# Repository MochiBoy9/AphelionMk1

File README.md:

# AphelionMk1
whoa! cool hack club project i'm making as a starter to cad and stuff

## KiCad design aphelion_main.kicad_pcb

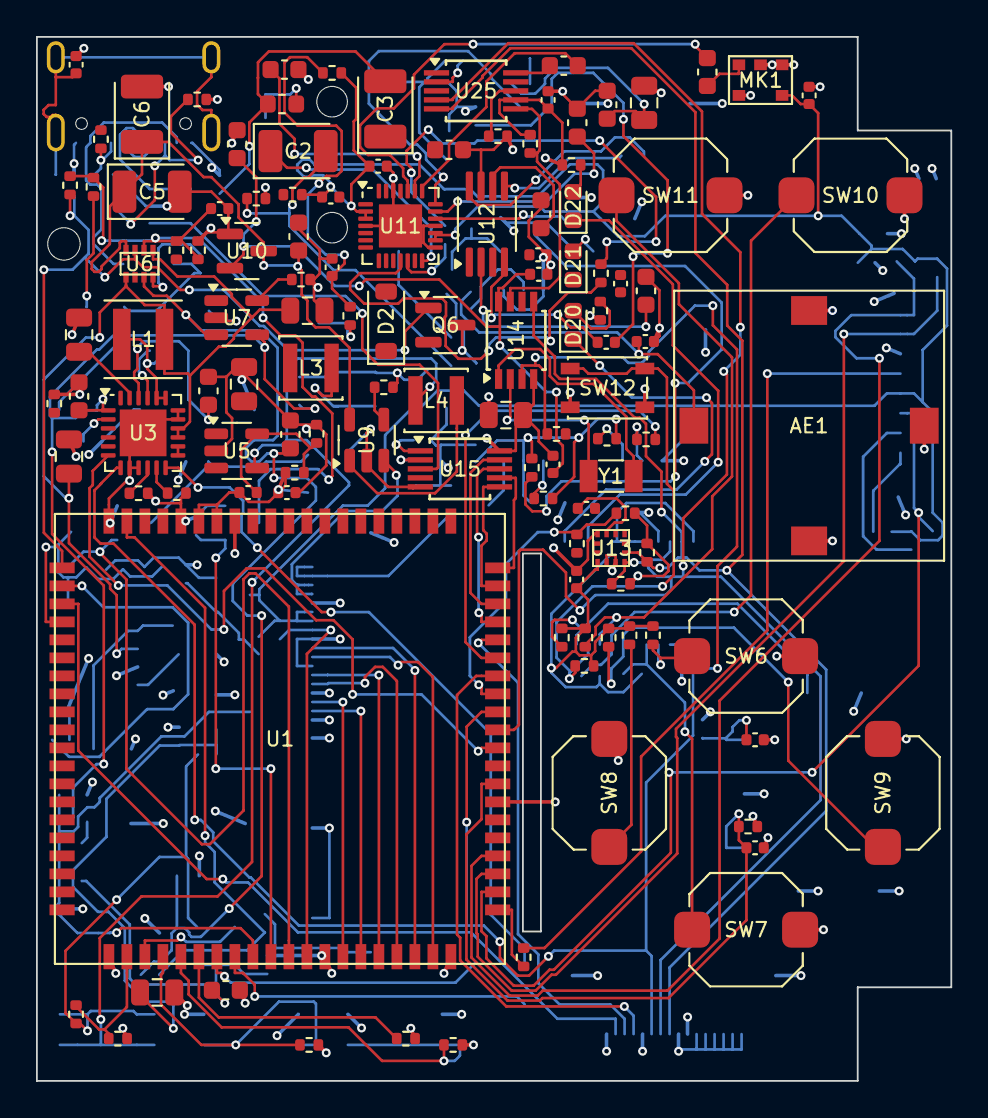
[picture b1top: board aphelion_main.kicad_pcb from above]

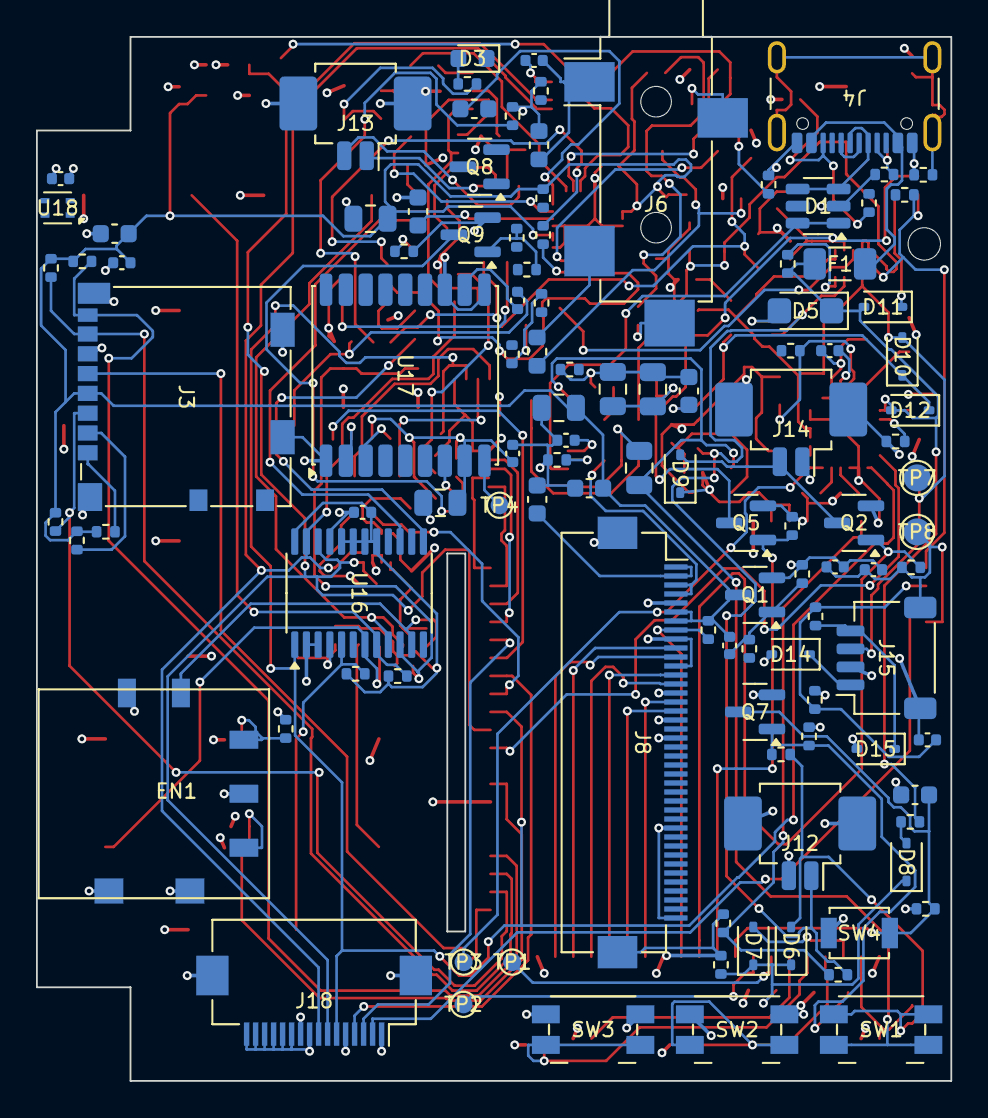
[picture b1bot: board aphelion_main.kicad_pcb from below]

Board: 4 copper layers, 50.8 x 58.0 mm, 232 parts (111 on the bottom side), 157 nets.

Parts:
AE1: 15 x 15 x 4 mm ceramic patch, 1575 MHz, surface m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; PATCH_15_SMD
C2, C3, C5, C6: 220 uF; CP_EIA-3528-15_AVX-H
C101: 4.7n; C_0402_1005Metric
C102, C111, C122, C124, C125, C126, C129, C130, C131, C132, C136, C137, C141, C145, C152, C153, C157, C158, C159, C160, C164: 100n; C_0402_1005Metric
C103, C112, C113, C118, C120, C121, C128, C142, C143, C146, C155, C156, C161, C162: 1u; C_0603_1608Metric
C104, C107, C108, C109, C114, C119, C123, C127, C135, C154, C163: 10u; C_0805_2012Metric
C105, C148, C165: 4.7u; C_0603_1608Metric
C106: 47n; C_0402_1005Metric
C110, C133, C134: 10n; C_0402_1005Metric
C115, C116: 22u; C_0805_2012Metric
C117: 22p; C_0402_1005Metric
C138, C144: 100p; C_0402_1005Metric
C139, C140: not fitted (tuning); C_0402_1005Metric
C147: 1u 50V; C_0603_1608Metric
C149, C150, C151: 10u; C_0603_1608Metric
D1: USBLC6-2SC6; SOT-23-6
D2: B0540W; D_SOD-123
D3: amber; LED_0603_1608Metric
D5: SMF12A; D_SMF
D6, D7, D8, D9, D11: 1N4148W; D_SOD-323
D10, D12: BAT54; D_SOD-323
D14, D15: ESD; D_SOD-323
D20: green; LED_0603_1608Metric
D21: red; LED_0603_1608Metric
D22: blue; LED_0603_1608Metric
EN1: thumbwheel encoder with push; THUMBWHEEL_ENC
F1: 2 A PTC; Fuse_1206_3216Metric
FB1: ferrite bead, 0402; R_0402_1005Metric
H1: M1.6 clamp screw; HOLE_1.8
J3: 104031-0811; microSD_HC_Molex_104031-0811
J4: USB4105-GF-A; USB_C_Receptacle_GCT_USB4105-xx-A_16P_TopMnt_Horizontal
J6: SJ-3524-SMT; Jack_3.5mm_CUI_SJ-3524-SMT_Horizontal
J8: FH12-40S-0.5SH; Hirose_FH12-40S-0.5SH_1x40-1MP_P0.50mm_Horizontal
J12, J13, J14: 2-pin 1.25 mm; Molex_PicoBlade_53261-0271_1x02-1MP_P1.25mm_Horizontal
J15: JST-SH 4-pin, side entry; JST_SH_SM04B-SRSS-TB_1x04-1MP_P1.00mm_Horizontal
J18: FH12-16S-0.5SH; Hirose_FH12-16S-0.5SH_1x16-1MP_P0.50mm_Horizontal
L1: 2.2 uH; L_Coilcraft_XxL4020
L3: 2.2 uH; L_Sunlord_SWPA3015S
L4: 10 uH; L_Sunlord_SWPA3015S
L5: ferrite bead, 600 ohm at 100 MHz, 0.15 ohm or les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; L_0603_1608Metric
L6, L7: ferrite bead, 2.5 kohm at 100 MHz; L_0603_1608Metric
MK1: analogue MEMS, top port; MIC_TOP_3.5x2.65
Q1, Q9: AO3401A; SOT-23
Q2, Q5, Q6, Q7, Q8: AO3400; SOT-23
R101, R120, R122, R123, R128, R175: 1M; R_0402_1005Metric
R102, R103: 5.1k; R_0402_1005Metric
R104, R105, R133, R135, R137, R138, R143, R145, R146, R155, R159, R166, R176, R177, R178, R181, R182, R183, R184, R185: 10k; R_0402_1005Metric
R106: 22k; R_0402_1005Metric
R107, R115, R118, R119, R126, R127, R129, R134, R136, R141, R142, R144, R147, R148, R149, R150, R151, R152, R153, R154, R156, R167, R174, R179: 100k; R_0402_1005Metric
R108: 330R; R_0402_1005Metric
R109, R110: 15k; R_0402_1005Metric
R111: 5.23k; R_0402_1005Metric
R112: 30.1k; R_0402_1005Metric
R113, R158: 1k; R_0402_1005Metric
R114: 232k; R_0402_1005Metric
R116: 180k; R_0402_1005Metric
R117: 1.5M; R_0402_1005Metric
R121: 470k; R_0402_1005Metric
R124: 16.5k; R_0402_1005Metric
R125: 453k; R_0402_1005Metric
R130: 390k; R_0402_1005Metric
R131: 2.2M; R_0402_1005Metric
R132: 4.7M; R_0402_1005Metric
R139, R140, R170, R171: 2.2k; R_0402_1005Metric
R157: 0R, fit only with the u-blox part; R_0402_1005Metric
R160, R162: 1.5k; R_0402_1005Metric
R161: 3.3k; R_0402_1005Metric
R163: 0R, fit once pad 3 is confirmed as a ground; R_0402_1005Metric
R164: 0R, fit once pad 8 is confirmed as a ground; R_0402_1005Metric
R165: 47k; R_0402_1005Metric
R168: 5.1R; R_0402_1005Metric
R169: 47R; R_0402_1005Metric
R172, R173: 4.7k; R_0402_1005Metric
R180: 22R; R_0402_1005Metric
SW1, SW2, SW3: EVQ-P7 class; Panasonic_EVQPUJ_EVQPUA
SW4: tact; SW_SPST_B3U-1000P
SW6, SW7, SW8, SW9, SW10, SW11: 6 x 6 x 5 mm tact; SW_Push_1TS009xxxx-xxxx-xxxx_6x6x5mm
SW12: 4.2 x 3.2 mm tact; SW_SPST_PTS810
TP1: TX; TestPoint_Pad_D1.0mm
TP2: RX; TestPoint_Pad_D1.0mm
TP3: QON; TestPoint_Pad_D1.0mm
TP4: GPS reset; TestPoint_Pad_D1.0mm
TP7: CELL +; TestPoint_Pad_D1.5mm
TP8: CELL -; TestPoint_Pad_D1.5mm
U1: ESP32-P4-Module; P4_MODULE_25x25
U3: SY6970; QFN-24-1EP_4x4mm_P0.5mm_EP2.6x2.6mm
U5: TLV62569; SOT-23-5
U6: TPS2116; SOT-583-8
U7: TP4054; SOT-23-5
U9: SY7200; SOT-23-5
U10: XC6206P332; SOT-23
U11: ES8388; QFN-28-1EP_4x4mm_P0.4mm_EP2.4x2.4mm
U12: NS4150B; MSOP-8_3x3mm_P0.65mm
U13: QMA6100P; LGA-12_2x2
U14: BM8563; TSSOP-8_3x3mm_P0.65mm
U15: FSUSB42; MSOP-10_3x3mm_P0.5mm
U16: XL9555; TSSOP-24_4.4x7.8mm_P0.65mm
U17: Quectel L76K (u-blox MAX-M10S fits the same pads); ublox_MAX
U18: Sensirion SHT40; Sensirion_DFN-4_1.5x1.5mm_P0.8mm_SHT4x_NoCentralPad
U25: RDA5807M; MSOP-10_3x3mm_P0.5mm
Y1: 32.768 kHz; Crystal_SMD_3215-2Pin_3.2x1.5mm

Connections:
+3V3: C102.1, C115.1, C116.1, C117.1, C124.1, C125.1, C126.1, C127.1, C141.1, C145.1, D1.5, D9.1, J14.1, J18.10, L3.2, Q1.2, Q9.2, R118.2, R125.1, R134.2, R135.2, R136.2, R137.2, R138.2, R139.2, R140.2, R141.2, R142.2, R145.2, R146.2, R160.1, R161.1, R162.1, R165.2, U1.54, U1.55, U15.1, U18.3, U25.7
+3V3_AON: C121.1, C129.1, C130.1, C131.1, C132.1, C137.1, R147.2, R148.2, R149.2, R150.2, R151.2, R152.2, R153.2, R154.2, R156.2, U10.2, U13.1, U13.9, U14.8, U16.17, U16.18, U16.19, U16.20, U16.24, U17.6
+3V3_GNSS: C135.1, C136.1, FB1.2, R157.2, R159.2, U17.8
+3V3_SW: C122.2, C123.1, C146.1, C152.1, C153.1, C154.1, C157.1, C164.1, C165.1, J3.4, J8.6, J8.7, MK1.5, Q1.3, R166.2, R170.2, R171.2, R175.2, R181.2, R182.2, R183.2, R184.2, R185.2, U11.2, U11.3, U11.16, U11.17
AMP_EN: Q8.2, R179.1, U12.1
AMP_EN_DRV: Q8.3, U1.44
AON_INT: J18.6, R141.1, U1.32, U3.7, U14.3, U16.1
BL_A: C147.1, D2.1, J8.1, J8.2
BL_K: J8.3, J8.4, R168.1, U9.3
BL_PWM: R167.1, U1.42, U9.4
BL_SENSE: Q6.3, R168.2, R169.1
BL_SW: D2.2, L4.2, U9.1
BOOT_SEL: R138.1, U1.6
BRIDGE_CHG_IN: C112.1, D10.1, D12.1, U7.4
BRIDGE_PROG: R124.1, U7.5
BTN_FA: R151.1, SW10.1, U16.8
BTN_FB: R152.1, SW11.1, U16.9
BTN_MENU: R153.1, SW12.1, U16.10
BTN_PTT: R136.1, SW2.1, U1.4
BTN_PWR_SENSE: R129.2, R130.1, U1.2
BTN_REC: R137.1, SW3.1, U1.5
BUCK_FB: C117.2, R125.2, R126.1, U5.5
BUCK_SW: L3.1, U5.3
CC1: J4.A5, R102.1, R104.1
CC1_SENSE: R104.2, U1.57
CC2: J4.B5, R103.1, R105.1
CC2_SENSE: R105.2, U1.58
CHG_BTST: C106.1, U3.21
CHG_DM: R110.1, U3.3
CHG_DP: R109.1, U3.2
CHG_ILIM: R108.1, U3.10
CHG_LED_A: D3.2, R113.2
CHG_PMID: C104.1, U3.23
CHG_QON: TP3.1, U3.12
CHG_REGN: C105.1, R111.1, U3.22
CHG_STAT: D3.1, U3.4
CHG_SW: C106.2, L1.1, U3.19, U3.20
CLK_32K: R165.1, U14.7, U25.6
CODEC_ADCVREF: C150.1, U11.19
CODEC_VMID: C151.1, U11.20
CODEC_VREF: C149.1, U11.10
D11_K: D11.1, R116.1
D20_A: D20.2, R160.2
D21_A: D21.2, R161.2
D22_A: D22.2, R162.2
DBG_RX: TP2.1, U1.8
DBG_TX: TP1.1, U1.7
DP_DOWN: R148.1, SW7.1, U16.5
DP_LEFT: R149.1, SW8.1, U16.6
DP_RIGHT: R150.1, SW9.1, U16.7
DP_UP: R147.1, SW6.1, U16.4
DSI_CLK_N: J8.13, U1.16
DSI_CLK_P: J8.14, U1.17
DSI_D0_N: J8.10, U1.18
DSI_D0_P: J8.11, U1.19
DSI_D1_N: J8.16, U1.14
DSI_D1_P: J8.17, U1.15
ENC_A: C133.1, EN1.A, R145.1, U1.28
ENC_B: C134.1, EN1.B, R146.1, U1.29
ENC_SW: EN1.S1, R154.1, U16.11
EN_3V3SW_N: R133.1, U1.43
FM_ANT: C144.2, U25.2
FM_L: C142.1, U25.10
FM_L_C: C142.2, U11.22
FM_P3: R163.1, U25.3
FM_P8: R164.1, U25.8
FM_R: C143.1, U25.9
FM_R_C: C143.2, U11.21
FORCE_BRIDGE: Q5.1, R119.1, U1.10
GND: AE1.2, C5.2, C6.2, C101.2, C102.2, C103.2, C104.2, C105.2, C107.2, C108.2, C109.2, C110.2, C111.2, C112.2, C113.2, C114.2, C115.2, C116.2, C118.2, C119.2, C120.2, C121.2, C123.2, C124.2, C125.2, C126.2, C127.2, C128.2, C129.2, C130.2, C131.2, C132.2, C133.2, C134.2, C135.2, C136.2, C137.2, C139.2, C140.2, C141.2, C145.2, C146.2, C147.2, C148.2, C149.2, C150.2, C151.2, C152.2, C153.2, C154.2, C155.2, C157.2, C158.2, C161.2, C162.2, C163.2, C164.2, C165.2, D1.2, D5.2, D14.2, D15.2, EN1.C, EN1.MP, EN1.S2, J3.6, J3.11, J4.A1, J4.A12, J4.B1, J4.B12, J8.5, J8.9, J8.12, J8.15, J8.18, J8.20, J8.30, J8.40, J8.MP, J12.2, J12.MP, J13.MP, J14.MP, J15.2, J15.MP, J18.1, J18.5, J18.9, J18.11, J18.12, J18.13, J18.14, J18.15, J18.16, J18.MP, L5.2, MK1.2, MK1.3, MK1.4, Q2.2, Q5.2, Q6.2, Q7.2, R101.2, R102.2, R103.2, R106.2, R107.2, R108.2, R109.2, R110.2, R112.2, R115.2, R119.2, R121.2, R123.2, R124.2, R126.2, R128.2, R130.2, R132.2, R144.2, R163.2, R164.2, R167.2, R169.2, R172.2, R173.2, R178.2, R179.2, SW2.2, SW3.2, SW4.2, SW6.2, SW7.2, SW8.2, SW9.2, SW10.2, SW11.2, SW12.2, TP8.1, U1.1, U1.13, U1.20, U1.27, U1.53, U1.56, U1.60, U1.64, U3.8, U3.9, U3.17, U3.18, U3.25, U5.2, U6.4, U7.2, U9.2, U10.1, U11.4, U11.15, U11.18, U11.26, U11.29, U12.7, U13.2, U13.3, U13.10, U14.4, U15.5, U15.10, U16.2, U16.3, U16.12, U16.21, U17.1, U17.10, U17.12, U18.4, U25.1
GNSS_ANT: AE1.1, C138.2, C140.1
GNSS_EN_N: R155.1, U16.16
GNSS_RF: C138.1, C139.1, U17.11
GNSS_RST: TP4.1, U17.9
GNSS_RXD: R159.1, U17.3
GNSS_SW: FB1.1, Q9.3
GNSS_TX: R158.2, U1.35
GNSS_TXD: R158.1, U17.2
GNSS_VIO: R157.1, U17.7
HAPTIC: Q2.1, R144.1, U1.11
HPL_C: C2.1, U11.14
HPR_C: C3.1, U11.13
HP_DET: C158.1, R174.2, R175.1, U1.45
HP_L: C2.2, L6.1, R172.1
HP_L_J: J6.T, L6.2
HP_R: C3.2, L7.1, R173.1
HP_RET: C144.1, J6.S, L5.1
HP_R_J: J6.R, L7.2
HP_SW: J6.TN, R174.1
I2C0_SCL: J18.7, R140.1, U1.31, U3.5, U13.4, U14.6, U16.22, U18.2, U25.4
I2C0_SDA: J18.8, R139.1, U1.30, U3.6, U13.5, U14.5, U16.23, U18.1, U25.5
I2C1_SCL: R171.1, U1.47, U11.28
I2C1_SDA: R170.1, U1.46, U11.27
I2S_BCLK: U1.49, U11.5
I2S_DIN: U1.52, U11.8
I2S_DOUT: U1.51, U11.6
I2S_MCLK: U1.48, U11.1
I2S_WS: U1.50, U11.7
IMU_INT: R142.1, R143.2, U1.33
IMU_INT_S: R143.1, U13.6
LCD_RST: J8.8, R166.1, U1.12
LED_LINK_K: D22.1, U16.15
LED_LOW_K: D21.1, U16.14
LED_ON_K: D20.1, U16.13
LONG_RESET: C119.1, Q7.1, R131.2, R132.1
MIC_AC: C156.2, U11.24
MIC_OUT: C156.1, MK1.1
MIC_REF: C155.1, U11.23
MOTOR_N: D9.2, J14.2, Q2.3
MUX_PR1: C110.1, Q5.3, R114.2, R115.1, R116.2, R117.2, U6.6
MUX_ST: Q6.1, Q8.1, R117.1, R118.1, U1.61, U6.7
PACK_DET: C111.1, R120.2, R121.1, U1.62
PACK_NTC: D14.1, J15.1, R111.2, R112.1, U3.11
PACK_SW: D15.1, J15.4, R114.1, R120.1
PWR_BTN: D6.2, R129.1, R131.1, SW1.2
PWR_EN: C118.1, D6.1, D7.1, D8.1, R128.1, U5.1
PWR_HOLD: D7.2, U1.3
Q1_G: C122.1, Q1.1, R133.2, R134.1
Q9_G: Q9.1, R155.2, R156.1
RESET: C128.1, Q7.3, R135.1, SW4.1, U1.9
RF_MISO: J18.2, U1.63
RF_MOSI: J18.3, U1.36
RF_SCK: J18.4, U1.34
RTC_X1: U14.1, Y1.1
RTC_X2: U14.2, Y1.2
SD_CLK: J3.5, R180.2
SD_CLK_R: R180.1, U1.21
SD_CMD: J3.3, R181.1, U1.22
SD_D0: J3.7, R182.1, U1.23
SD_D1: J3.8, R183.1, U1.24
SD_D2: J3.1, R184.1, U1.25
SD_D3: J3.2, R185.1, U1.26
SHIELD: C101.1, J4.S1, R101.1
SPK_BYP: C161.1, U12.2
SPK_INN: C160.1, U12.4
SPK_INN_R: C160.2, R178.1
SPK_INP: C159.2, U12.3
SPK_L: R176.1, U11.12
SPK_N: J13.2, U12.8
SPK_P: J13.1, U12.5
SPK_R: R177.1, U11.11
SPK_SUM: C159.1, R176.2, R177.2
USB_DM: D1.3, D1.4, J4.A7, J4.B7, U15.4
USB_DP: D1.1, D1.6, J4.A6, J4.B6, U15.3
USB_HS_N: U1.37, U15.8
USB_HS_P: U1.38, U15.9
USB_JTAG_N: U1.39, U15.6
USB_JTAG_P: U1.40, U15.7
USB_SEL: R107.1, U1.41, U15.2
VBRIDGE: C113.1, J12.1, R122.1, U6.3, U7.3
VBR_SENSE: R122.2, R123.1, U1.59
VBUS: C103.1, D5.1, D11.2, D12.2, F1.2, R106.1, R127.1, U3.1
VBUS_IN: F1.1, J4.A4, J4.A9, J4.B4, J4.B9
VBUS_PE: D8.2, R127.2
VPACK: C109.1, TP7.1, U3.13, U3.14
VSYS: C5.1, C6.1, C114.1, C120.1, C148.1, C162.1, C163.1, L4.1, R113.1, SW1.1, U5.4, U6.2, U6.8, U9.5, U10.3, U12.6
VSYS_MAIN: C107.1, C108.1, D10.2, J15.3, L1.2, U3.15, U3.16, U6.1, U6.5
